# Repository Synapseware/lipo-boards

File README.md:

LiPo Boards
===========

## Low-Voltage Cutoff boards
A project as an exercise in overkill: Lipo LVCO boards using ATTiny13's, voltage references and MOSFETs.  These boards specialize in ultra-low current draw while disabled (but not low enough to be safe).

Use at your own risk.

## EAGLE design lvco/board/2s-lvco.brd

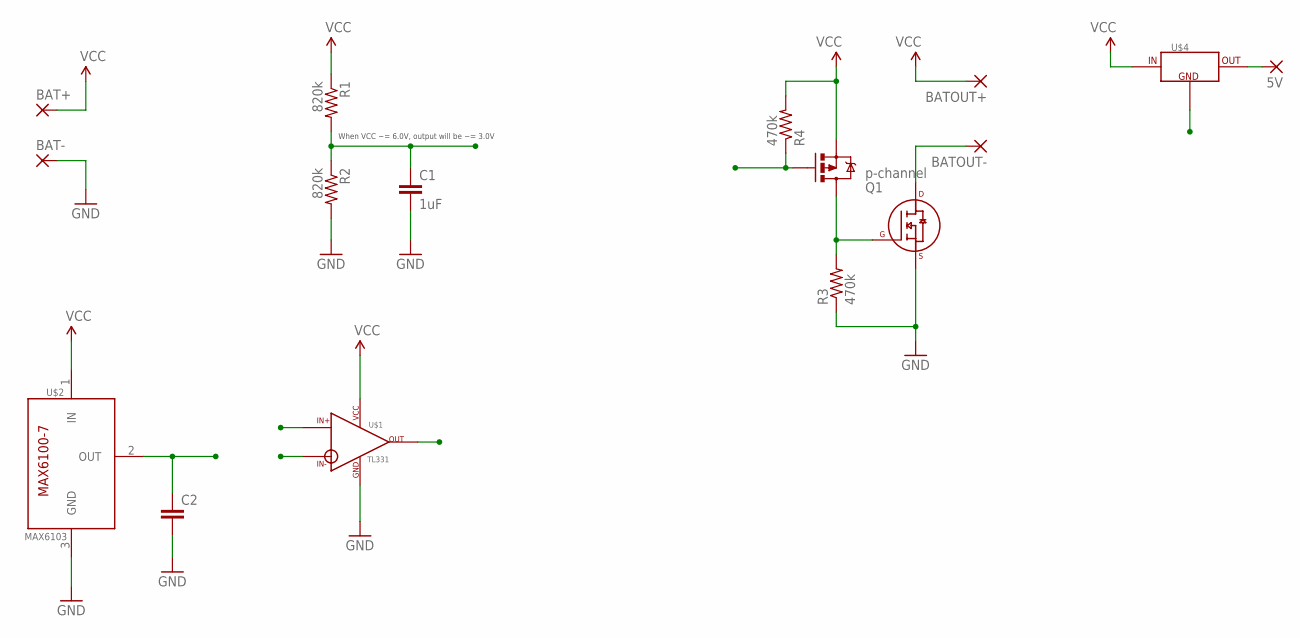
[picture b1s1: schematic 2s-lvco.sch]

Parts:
5V: WIREPADSMD2,54-5,08; SMD2,54-5,08
BAT+: WIREPADSMD2,54-5,08; SMD2,54-5,08
BAT-: WIREPADSMD2,54-5,08; SMD2,54-5,08
BATOUT+: WIREPADSMD2,54-5,08; SMD2,54-5,08
BATOUT-: WIREPADSMD2,54-5,08; SMD2,54-5,08
C1: 1uF; 0603-CAP
C2: CAP0603-CAP; 0603-CAP
Q1: p-channel; SOT23-3
R1, R2: 820k; 0603-RES
R3, R4: 470k; 0603-RES
U$1: TL331; SOT-23-5
U$2: MAX6103; SOT-23-3
U$3: RFD14N05L; TO-252AA
U$4: TPS715XX; SOT-23-5

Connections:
BATOUT-: BATOUT-.1, U$3.4 (D), U$4.2 (GND)
GND: BAT-.1, C1.2, C2.2, R2.2, R3.1, U$1.2 (GND), U$2.3 (GND), U$3.3 (S)
unnamed: Q1.3 (D), R3.2, U$3.1 (G)
unnamed: 5V.1, U$4.5 (OUT)
REF: C2.1, U$1.3 (IN+), U$2.2 (OUT)
SW: Q1.1 (G), R4.1, U$1.4 (OUT)
VCC: BAT+.1, BATOUT+.1, Q1.2 (S), R1.1, R4.2, U$1.5 (VCC), U$2.1 (IN), U$4.4 (IN)
VDIV_OUT: C1.1, R1.2, R2.1, U$1.1 (IN-)

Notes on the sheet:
When VCC ~= 6.0V, output will be ~= 3.0V

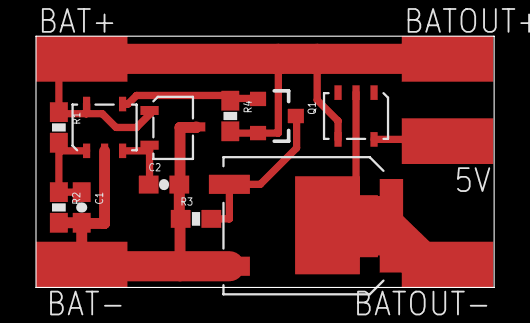
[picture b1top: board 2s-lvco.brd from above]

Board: 2 copper layers, 25.5 x 14.0 mm, 16 parts (0 on the bottom side), 8 nets.

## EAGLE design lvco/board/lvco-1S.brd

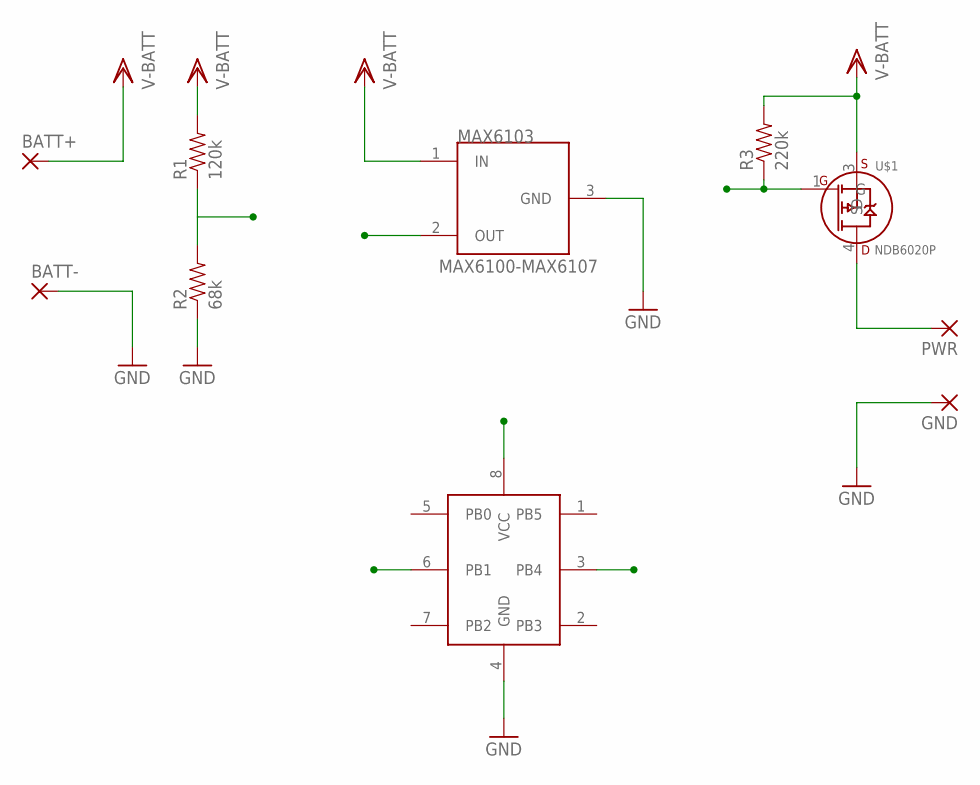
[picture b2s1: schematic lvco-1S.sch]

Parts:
BATT+: WIREPAD2,54/1,1; 2,54/1,1
BATT-: WIREPAD2,54/1,1; 2,54/1,1
GND: WIREPAD2,54/1,1; 2,54/1,1
MAX6103: MAX6100-MAX6107; SOT-23-3
PWR: WIREPAD2,54/1,1; 2,54/1,1
R1: 120k; 0805
R2: 68k; 0805
R3: 220k; 0805
U$1: NDB6020P; TO-263AB
U$2: ATTINY13; WSOIC-8

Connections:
GND: BATT-.1, GND.1, MAX6103.3 (GND), R2.1, U$2.4 (GND)
unnamed: PWR.1, U$1.4 (D)
REF-BATT: R1.1, R2.2, U$2.6 (PB1)
SW: R3.1, U$1.1 (G), U$2.3 (PB4)
VCC: MAX6103.2 (OUT), U$2.8 (VCC)
VSS: BATT+.1, MAX6103.1 (IN), R1.2, R3.2, U$1.3 (S)

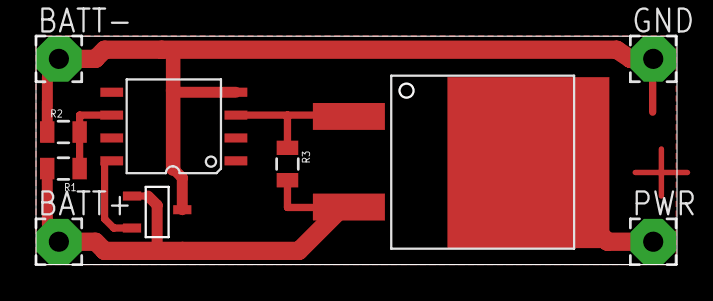
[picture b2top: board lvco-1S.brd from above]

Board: 2 copper layers, 35.5 x 12.6 mm, 10 parts (0 on the bottom side), 6 nets.

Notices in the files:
parts and their libraries:
SparkFun-Capacitors: Licensing: CC v3.0 Share-Alike You are welcome to use this library for commercial purposes.
